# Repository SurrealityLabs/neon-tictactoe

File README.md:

# neon-tictactoe
A piece of wall art that also plays Tic Tac Toe

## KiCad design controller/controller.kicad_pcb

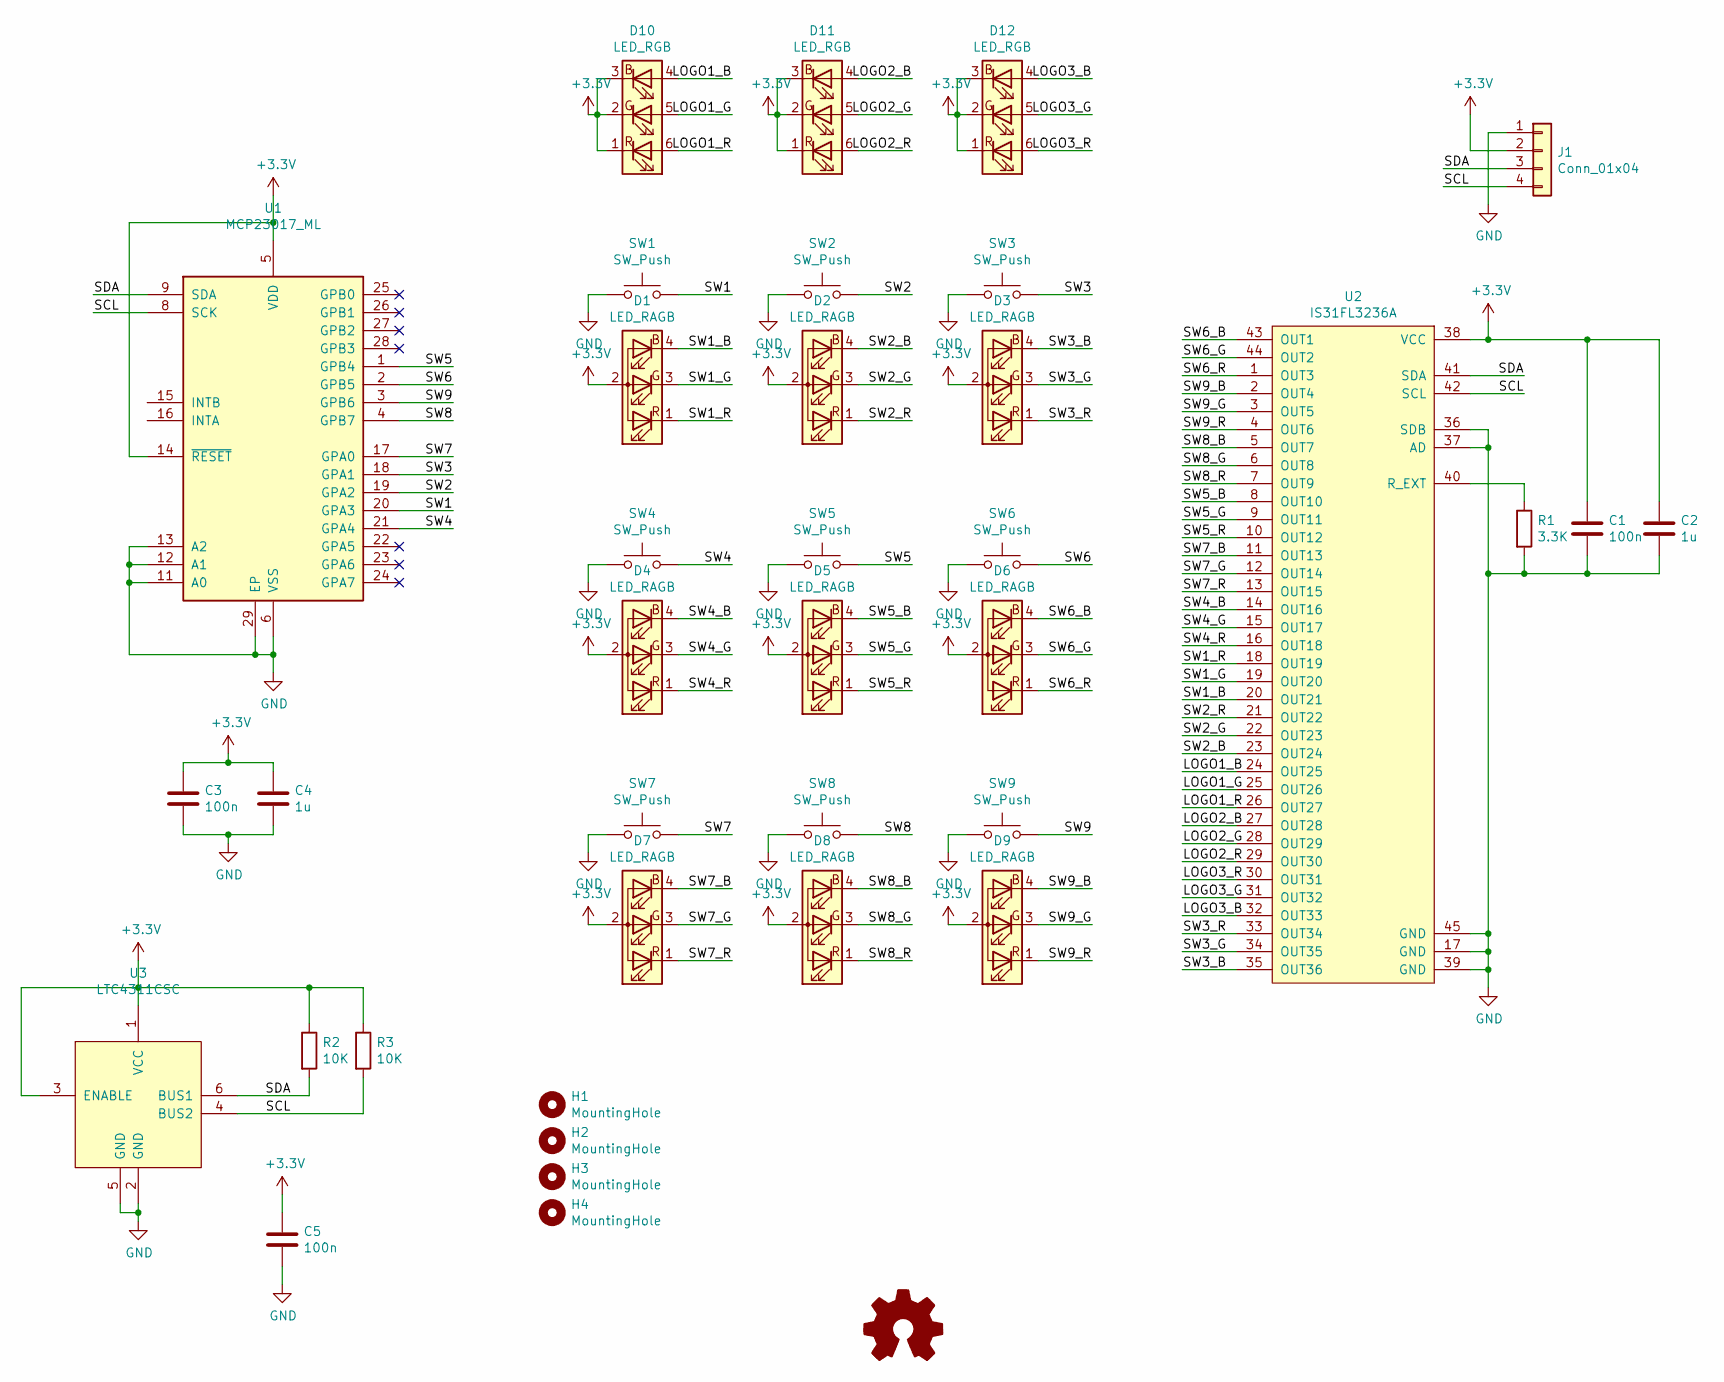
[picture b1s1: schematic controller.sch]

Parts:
C1, C3, C5: 100n; C_0603_1608Metric_Pad1.05x0.95mm_HandSolder
C2, C4: 1u; C_0603_1608Metric_Pad1.05x0.95mm_HandSolder
D1, D2, D3, D4, D5, D6, D7, D8, D9: LED_RAGB; LED-6526-RGB
D10, D11, D12: LED_RGB; LED_RGB_5050-6
H1, H2, H3, H4: MountingHole; MountingHole_3.2mm_M3_DIN965
J1: Conn_01x04; JST_PH_S4B-PH-SM4-TB_04x2.00mm_Angled
R1: 3.3K; R_0603_1608Metric_Pad0.98x0.95mm_HandSolder
R2, R3: 10K; R_0603_1608Metric_Pad0.98x0.95mm_HandSolder
SW1, SW2, SW3, SW4, SW5, SW6, SW7, SW8, SW9: SW_Push; SW_Cherry_MX_1.00u_PCB
U1: MCP23017_ML; QFN-28-1EP_6x6mm_P0.65mm_EP4.25x4.25mm
U2: IS31FL3236A; QFN-44-1EP_5x5mm_P0.4mm_EP2.45x2.45mm
U3: LTC4311CSC; SOT-363_SC-70-6

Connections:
+3V3: C1.1, C2.1, C3.1, C4.1, C5.1, D1.2 (A), D2.2 (A), D3.2 (A), D4.2 (A), D5.2 (A), D6.2 (A), D7.2 (A), D8.2 (A), D9.2 (A), D10.1 (RK), D10.2 (GK), D10.3 (BK), D11.1 (RK), D11.2 (GK), D11.3 (BK), D12.1 (RK), D12.2 (GK), D12.3 (BK), J1.2, R2.1, R3.1, U1.5 (VDD), U1.14 (~RESET~), U2.38 (VCC), U3.1 (VCC), U3.3 (ENABLE)
/LOGO1_B: D10.4 (BA), U2.24 (OUT25)
/LOGO1_G: D10.5 (GA), U2.25 (OUT26)
/LOGO1_R: D10.6 (RA), U2.26 (OUT27)
/LOGO2_B: D11.4 (BA), U2.27 (OUT28)
/LOGO2_G: D11.5 (GA), U2.28 (OUT29)
/LOGO2_R: D11.6 (RA), U2.29 (OUT30)
/LOGO3_B: D12.4 (BA), U2.32 (OUT33)
/LOGO3_G: D12.5 (GA), U2.31 (OUT32)
/LOGO3_R: D12.6 (RA), U2.30 (OUT31)
/SCL: J1.4, R3.2, U1.8 (SCK), U2.42 (SCL), U3.4 (BUS2)
/SDA: J1.3, R2.2, U1.9 (SDA), U2.41 (SDA), U3.6 (BUS1)
/SW1: SW1.2, U1.20 (GPA3)
/SW1_B: D1.4 (BK), U2.20 (OUT21)
/SW1_G: D1.3 (GK), U2.19 (OUT20)
/SW1_R: D1.1 (RK), U2.18 (OUT19)
/SW2: SW2.2, U1.19 (GPA2)
/SW2_B: D2.4 (BK), U2.23 (OUT24)
/SW2_G: D2.3 (GK), U2.22 (OUT23)
/SW2_R: D2.1 (RK), U2.21 (OUT22)
/SW3: SW3.2, U1.18 (GPA1)
/SW3_B: D3.4 (BK), U2.35 (OUT36)
/SW3_G: D3.3 (GK), U2.34 (OUT35)
/SW3_R: D3.1 (RK), U2.33 (OUT34)
/SW4: SW4.2, U1.21 (GPA4)
/SW4_B: D4.4 (BK), U2.14 (OUT16)
/SW4_G: D4.3 (GK), U2.15 (OUT17)
/SW4_R: D4.1 (RK), U2.16 (OUT18)
/SW5: SW5.2, U1.1 (GPB4)
/SW5_B: D5.4 (BK), U2.8 (OUT10)
/SW5_G: D5.3 (GK), U2.9 (OUT11)
/SW5_R: D5.1 (RK), U2.10 (OUT12)
/SW6: SW6.2, U1.2 (GPB5)
/SW6_B: D6.4 (BK), U2.43 (OUT1)
/SW6_G: D6.3 (GK), U2.44 (OUT2)
/SW6_R: D6.1 (RK), U2.1 (OUT3)
/SW7: SW7.2, U1.17 (GPA0)
/SW7_B: D7.4 (BK), U2.11 (OUT13)
/SW7_G: D7.3 (GK), U2.12 (OUT14)
/SW7_R: D7.1 (RK), U2.13 (OUT15)
/SW8: SW8.2, U1.4 (GPB7)
/SW8_B: D8.4 (BK), U2.5 (OUT7)
/SW8_G: D8.3 (GK), U2.6 (OUT8)
/SW8_R: D8.1 (RK), U2.7 (OUT9)
/SW9: SW9.2, U1.3 (GPB6)
/SW9_B: D9.4 (BK), U2.2 (OUT4)
/SW9_G: D9.3 (GK), U2.3 (OUT5)
/SW9_R: D9.1 (RK), U2.4 (OUT6)
GND: C1.2, C2.2, C3.2, C4.2, C5.2, J1.1, R1.2, SW1.1, SW2.1, SW3.1, SW4.1, SW5.1, SW6.1, SW7.1, SW8.1, SW9.1, U1.6 (VSS), U1.11 (A0), U1.12 (A1), U1.13 (A2), U1.29 (EP), U2.17 (GND), U2.36 (SDB), U2.37 (AD), U2.39 (GND), U2.45 (GND), U3.2 (GND), U3.5 (GND)
unnamed: R1.1, U2.40 (R_EXT)

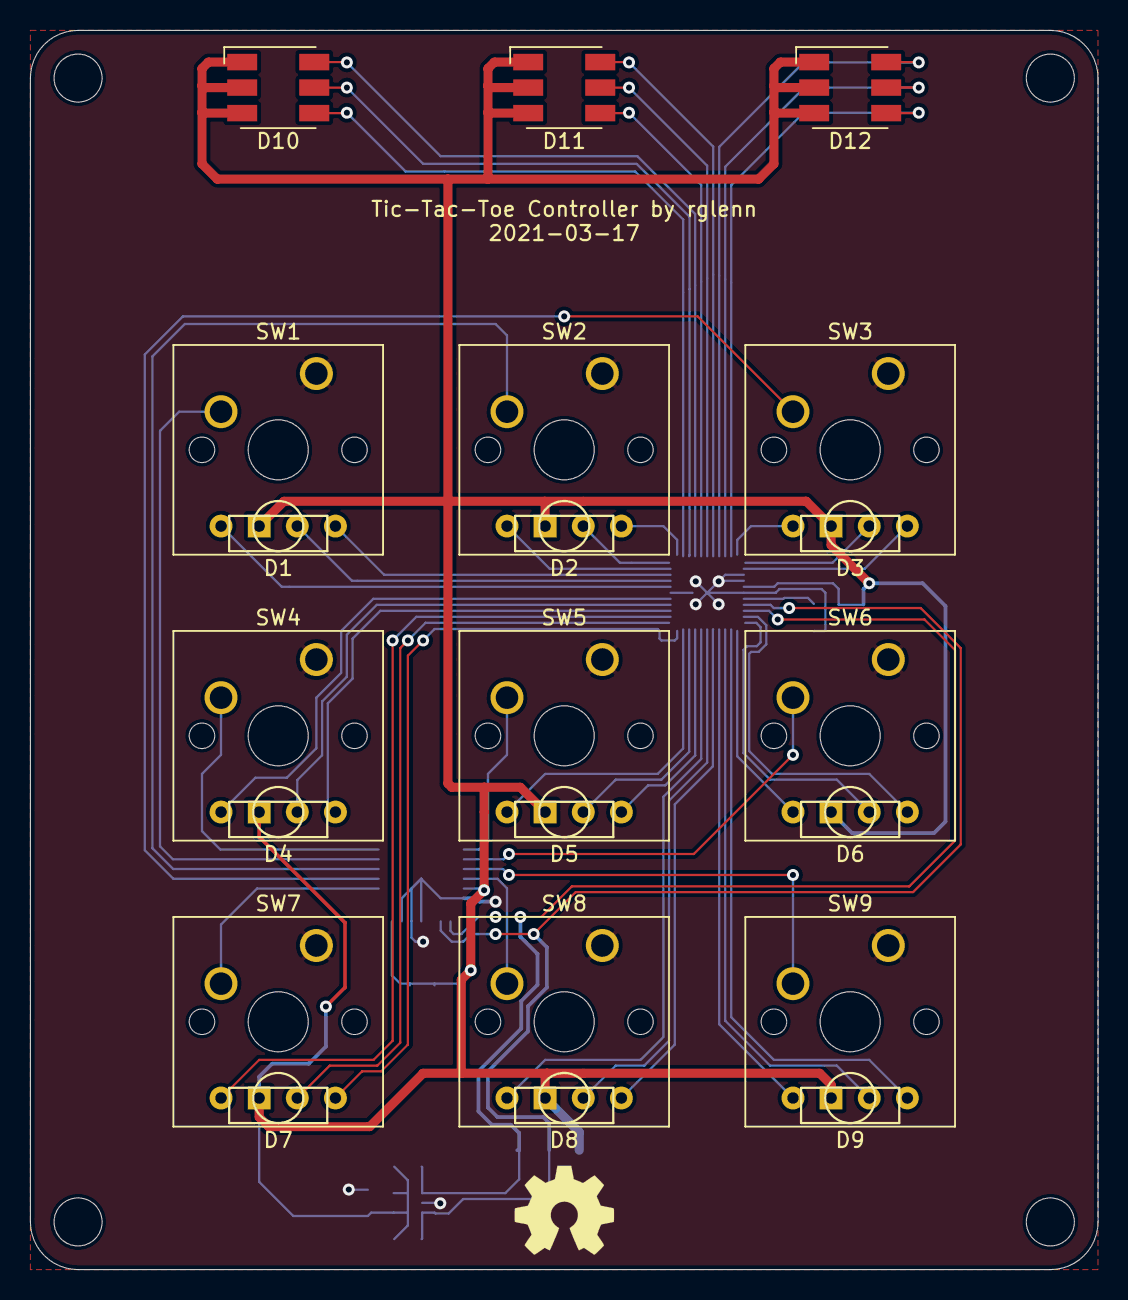
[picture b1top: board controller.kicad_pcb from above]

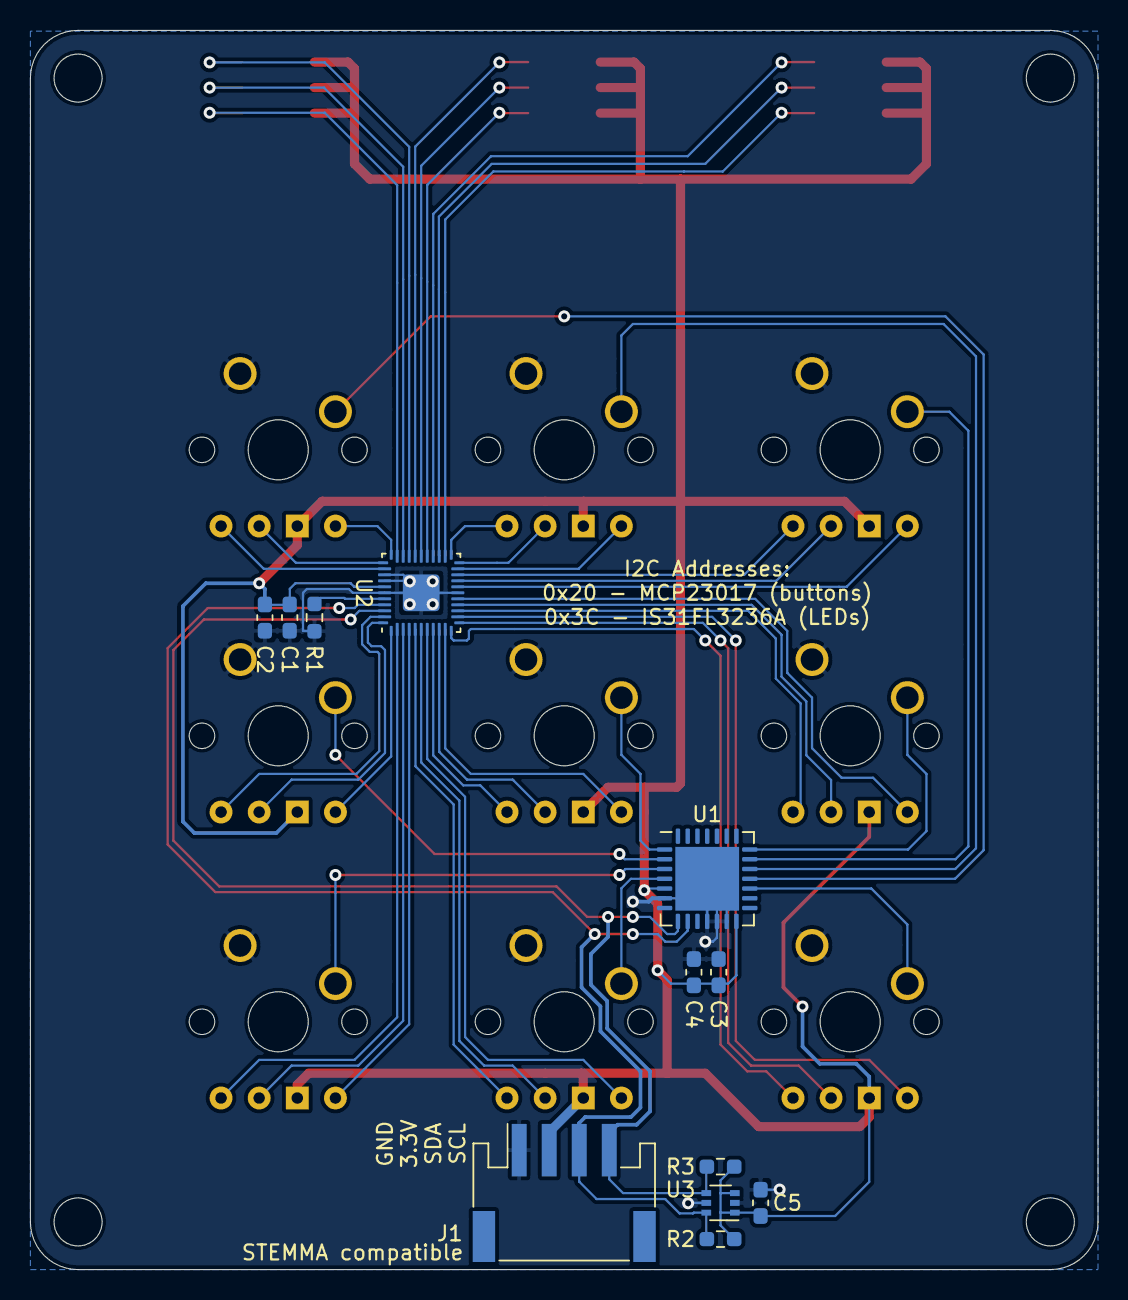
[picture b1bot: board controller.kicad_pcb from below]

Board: 2 copper layers, 71.1 x 82.6 mm, 37 parts (12 on the bottom side), 50 nets.

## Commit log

2021-03-21 Adding first rev of controller
